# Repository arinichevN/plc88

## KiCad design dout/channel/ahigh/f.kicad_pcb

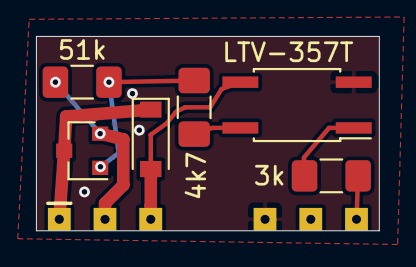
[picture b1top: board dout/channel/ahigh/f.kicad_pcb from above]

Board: 2 copper layers, 19.1 x 10.8 mm, 7 parts (0 on the bottom side), 8 nets.

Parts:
D1: 1N4148W; D_SOD-123
J1: dio_channel_i; dio_channel_im
Q1: BC807; SOT-23
R1: 51k; R_1206_3216Metric_Pad1.42x1.75mm_HandSolder
R2: 4k7; R_1206_3216Metric_Pad1.42x1.75mm_HandSolder
R3: 3k; R_1206_3216Metric_Pad1.42x1.75mm_HandSolder
U1: LTV-357T; SO-4_4.4x3.6mm_P2.54mm

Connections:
GND: J1.4, U1.2
IN: J1.6, R3.2
unnamed: Q1.1, R1.2, R2.1
unnamed: R2.2, U1.4
unnamed: R3.1, U1.1
OUT: D1.1, J1.1, Q1.3
VINM: D1.2, J1.3, U1.3
VINP: J1.2, Q1.2, R1.1

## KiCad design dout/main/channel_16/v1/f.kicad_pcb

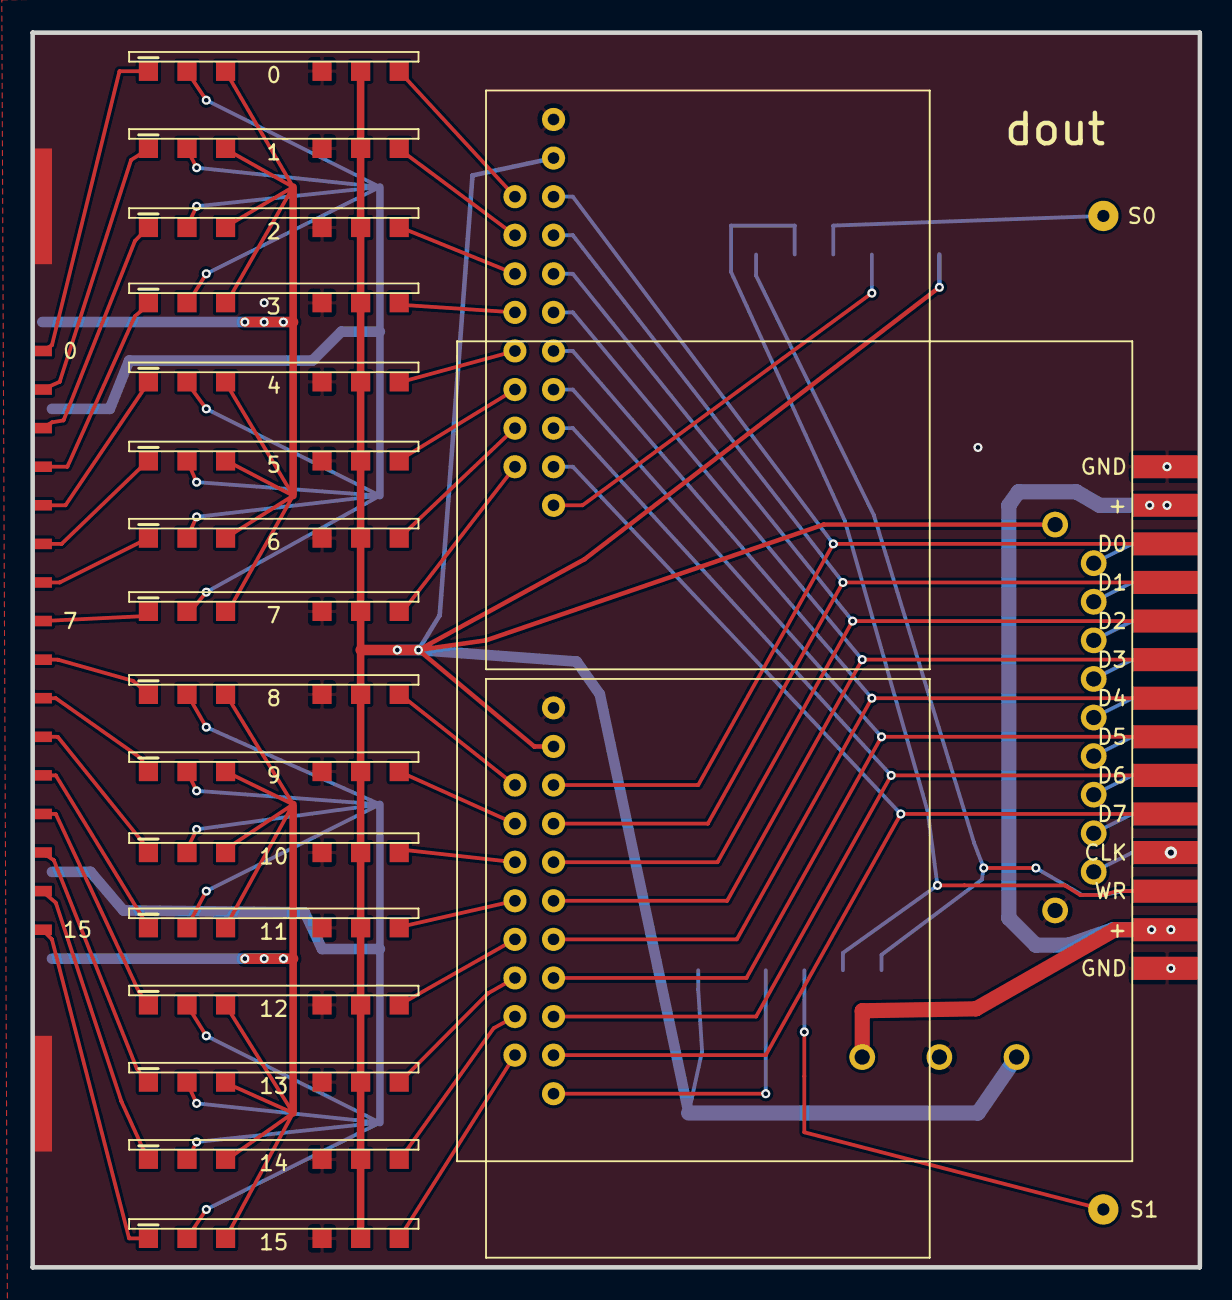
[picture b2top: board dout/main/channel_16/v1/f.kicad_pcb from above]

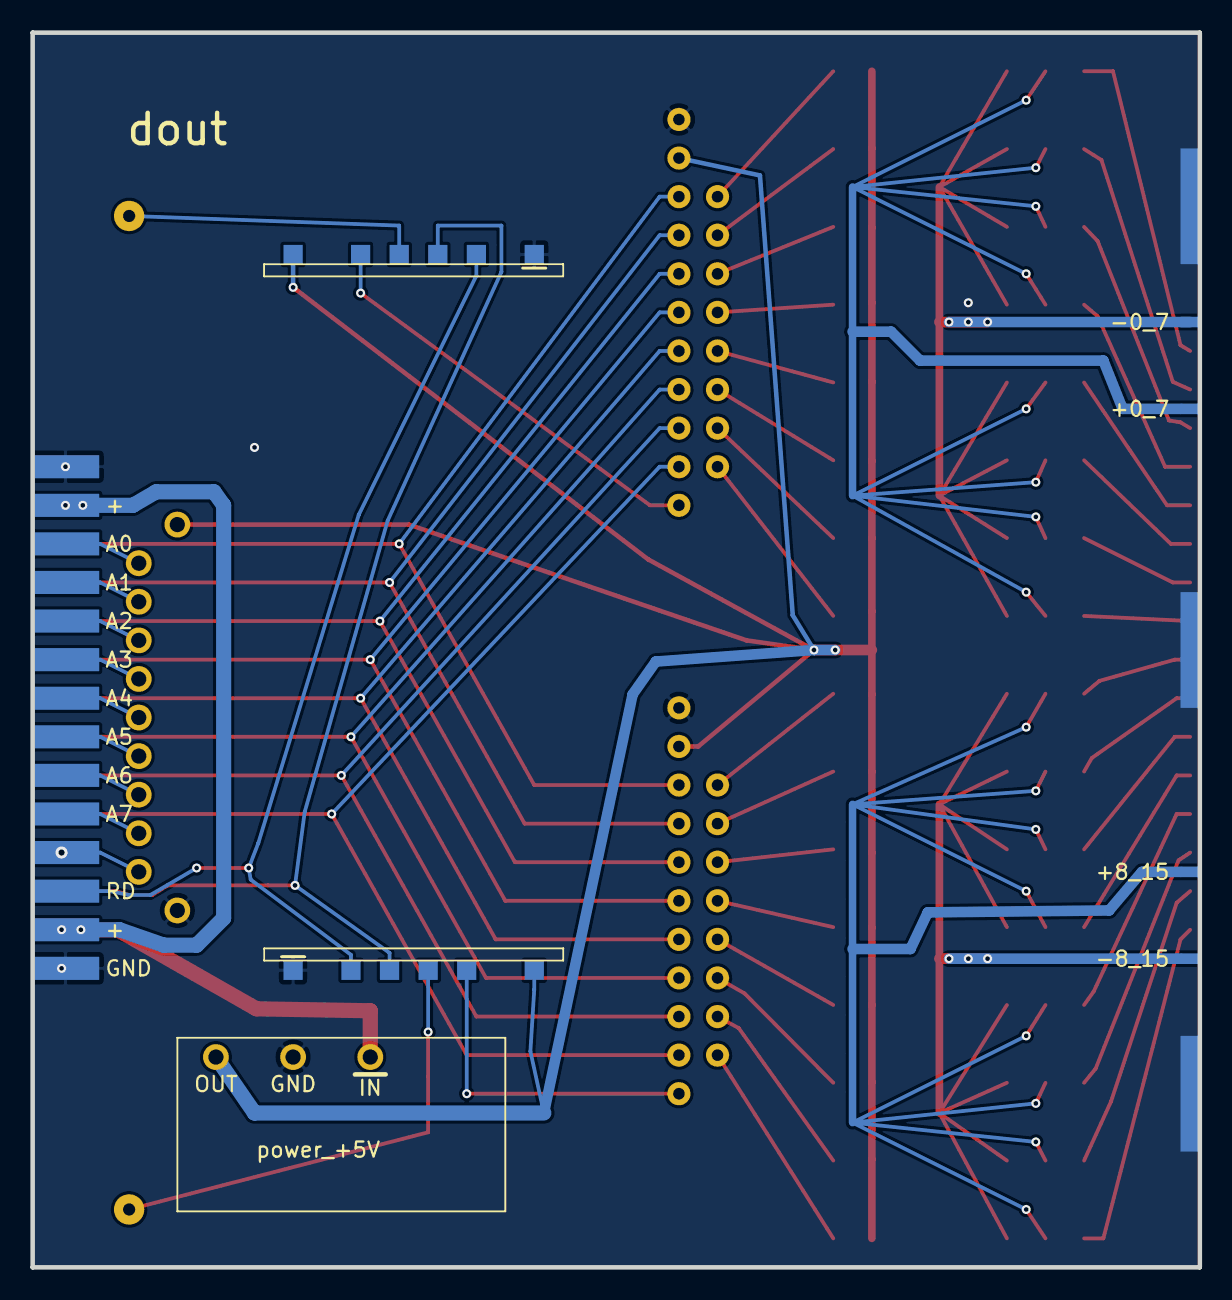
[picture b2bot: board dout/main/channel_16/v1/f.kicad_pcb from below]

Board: 2 copper layers, 76.8 x 81.3 mm, 26 parts (3 on the bottom side), 62 nets.

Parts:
J1: fm16_i; fm16_im
J2, J3, J4, J5, J6, J7, J8, J9, J10, J11, J12, J13, J14, J15, J16, J17: dio_channel_i
J18, J19: data_manager_i
J20, J21: wrs_i
J22: S0; SolderWirePad_1x01_Drill0.8mm
J23: S1; SolderWirePad_1x01_Drill0.8mm
J24: bus_i; bus_im
J25: selector4_i
J26: power_+5V; power_i

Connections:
+5V: J2.5, J3.5, J4.5, J5.5, J6.5, J7.5, J8.5, J9.5, J10.5, J11.5, J12.5, J13.5, J14.5, J15.5, J16.5, J17.5, J18.18, J19.18, J20.6, J21.6, J25.1, J26.2
A0: J24.5, J25.2
A1: J24.7, J25.3
A2: J24.9, J25.4
A3: J24.11, J25.5
A4: J24.13, J25.6
A5: J24.15, J25.7
A6: J24.17, J25.8
A7: J24.19, J25.9
CLK: J24.21, J24.22, J25.10
D0: J18.2, J19.2, J24.6
D1: J18.4, J19.4, J24.8
D2: J18.6, J19.6, J24.10
D3: J18.8, J19.8, J24.12
D4: J18.10, J19.10, J24.14
D5: J18.12, J19.12, J24.16
D6: J18.14, J19.14, J24.18
D7: J18.16, J19.16, J24.20
GND: J1.21, J1.22, J1.23, J1.24, J1.25, J2.4, J3.4, J4.4, J5.4, J6.4, J7.4, J8.4, J9.4, J10.4, J11.4, J12.4, J13.4, J14.4, J15.4, J16.4, J17.4, J18.17, J19.17, J20.1, J21.1, J24.1, J24.2, J24.27, J24.28, J25.11, J26.3
OPL0: J2.6, J18.1
OPL1: J3.6, J18.3
OPL2: J4.6, J18.5
OPL3: J5.6, J18.7
OPL4: J6.6, J18.9
OPL5: J7.6, J18.11
OPL6: J8.6, J18.13
OPL7: J9.6, J18.15
OPL8: J10.6, J19.1
OPL9: J11.6, J19.3
OPL10: J12.6, J19.5
OPL11: J13.6, J19.7
OPL12: J14.6, J19.9
OPL13: J15.6, J19.11
OPL14: J16.6, J19.13
OPL15: J17.6, J19.15
OUT0: J1.1, J2.1
OUT1: J1.2, J3.1
OUT2: J1.3, J4.1
OUT3: J1.4, J5.1
OUT4: J1.5, J6.1
OUT5: J1.6, J7.1
OUT6: J1.7, J8.1
OUT7: J1.8, J9.1
OUT8: J1.9, J10.1
OUT9: J1.10, J11.1
OUT10: J1.11, J12.1
OUT11: J1.12, J13.1
OUT12: J1.13, J14.1
OUT13: J1.14, J15.1
OUT14: J1.15, J16.1
OUT15: J1.16, J17.1
RD: J20.2, J21.2, J24.23
S0: J20.4, J22.1
S1: J21.4, J23.1
SW0: J18.19, J20.5
SW1: J19.19, J21.5
VM0_7: J1.17, J2.3, J3.3, J4.3, J5.3, J6.3, J7.3, J8.3, J9.3
VM8_15: J1.20, J10.3, J11.3, J12.3, J13.3, J14.3, J15.3, J16.3, J17.3
VP0_7: J1.18, J2.2, J3.2, J4.2, J5.2, J6.2, J7.2, J8.2, J9.2
VP8_15: J1.19, J10.2, J11.2, J12.2, J13.2, J14.2, J15.2, J16.2, J17.2
VPBUS: J24.3, J24.4, J24.25, J24.26, J26.1
WR: J20.3, J21.3, J24.24

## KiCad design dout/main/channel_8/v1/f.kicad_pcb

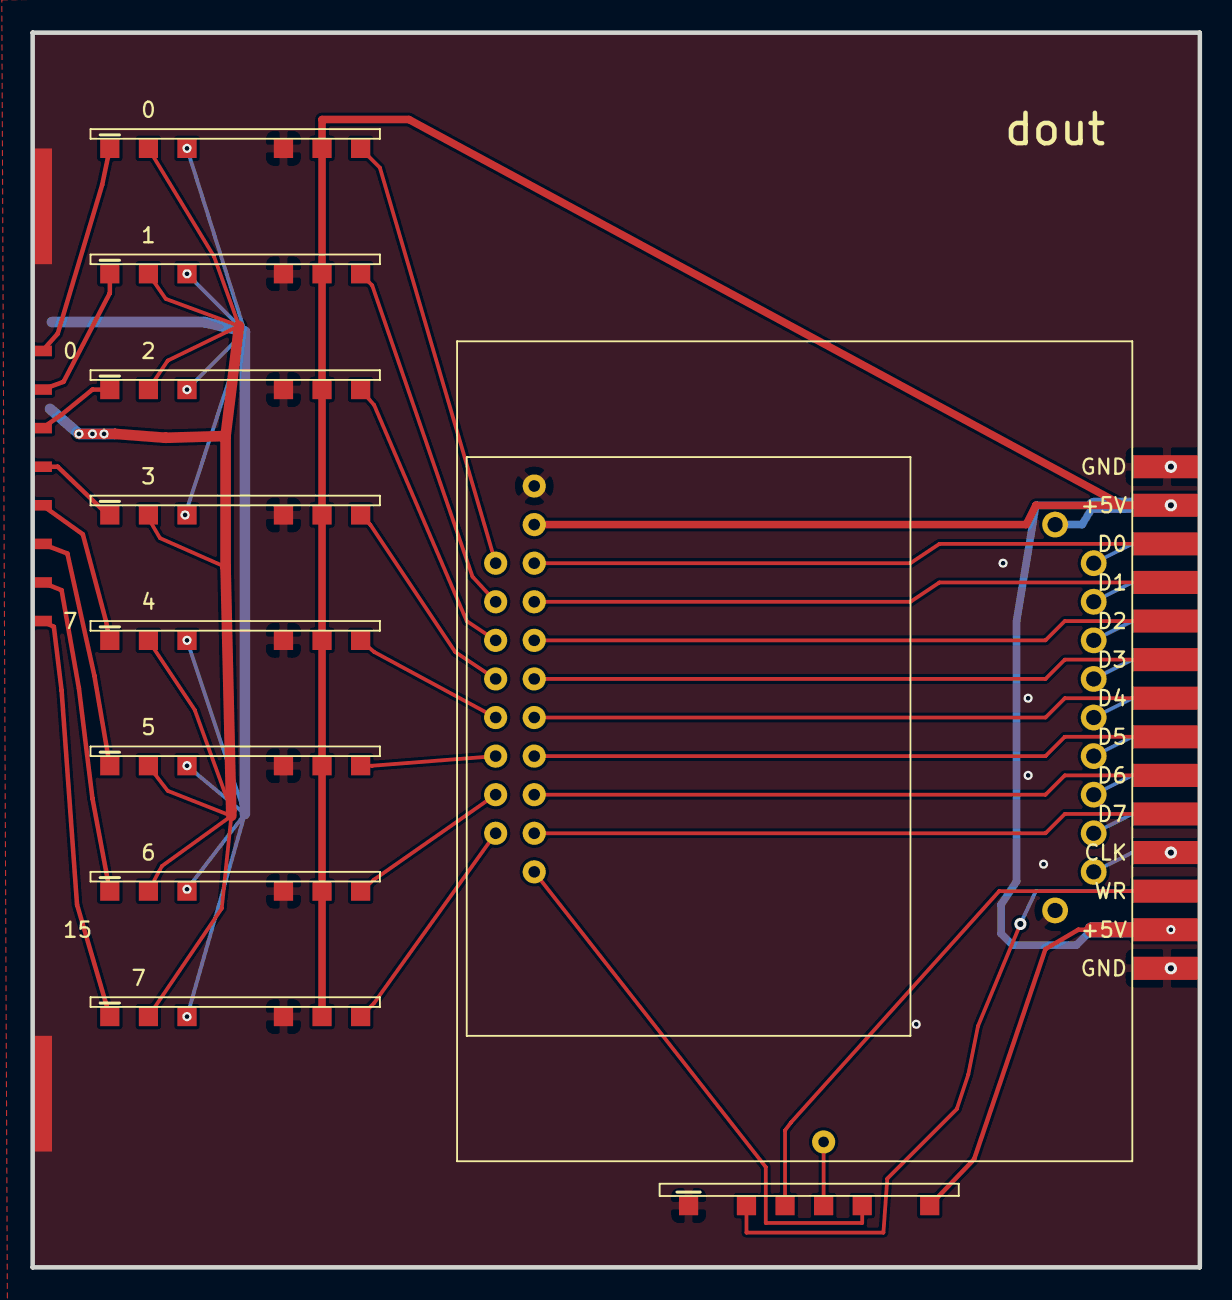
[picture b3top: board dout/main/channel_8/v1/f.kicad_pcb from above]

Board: 2 copper layers, 76.8 x 81.3 mm, 13 parts (0 on the bottom side), 41 nets.

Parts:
J1: fm16_i; fm16_im
J2, J3, J4, J5, J6, J7, J8, J9: dio_channel_i
J10: data_manager_i
J11: wrs_i
J12: selector4_i
J13: bus_i; bus_im

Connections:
+5V: J2.5, J3.5, J4.5, J5.5, J6.5, J7.5, J8.5, J9.5, J10.18, J11.6, J12.1, J13.3, J13.4, J13.25, J13.26
A0: J12.2, J13.5
A1: J12.3, J13.7
A2: J12.4, J13.9
A3: J12.5, J13.11
A4: J12.6, J13.13
A5: J12.7, J13.15
A6: J12.8, J13.17
A7: J12.9, J13.19
CLK: J12.10, J13.21, J13.22
D0: J10.2, J13.6
D1: J10.4, J13.8
D2: J10.6, J13.10
D3: J10.8, J13.12
D4: J10.10, J13.14
D5: J10.12, J13.16
D6: J10.14, J13.18
D7: J10.16, J13.20
GND: J1.21, J1.22, J1.23, J1.24, J1.25, J2.4, J3.4, J4.4, J5.4, J6.4, J7.4, J8.4, J9.4, J10.17, J11.1, J12.11, J13.1, J13.2, J13.27, J13.28
OPL0: J2.6, J10.1
OPL1: J3.6, J10.3
OPL2: J4.6, J10.5
OPL3: J5.6, J10.7
OPL4: J6.6, J10.9
OPL5: J7.6, J10.11
OPL6: J8.6, J10.13
OPL7: J9.6, J10.15
OUT0: J1.1, J2.1
OUT1: J1.2, J3.1
OUT2: J1.3, J4.1
OUT3: J1.4, J5.1
OUT4: J1.5, J6.1
OUT5: J1.6, J7.1
OUT6: J1.7, J8.1
OUT7: J1.8, J9.1
RD: J11.2, J13.23
S0: J11.4, J12.12
SW0: J10.19, J11.5
VM0_7: J1.17, J2.3, J3.3, J4.3, J5.3, J6.3, J7.3, J8.3, J9.3
VP0_7: J1.18, J2.2, J3.2, J4.2, J5.2, J6.2, J7.2, J8.2, J9.2
WR: J11.3, J13.24

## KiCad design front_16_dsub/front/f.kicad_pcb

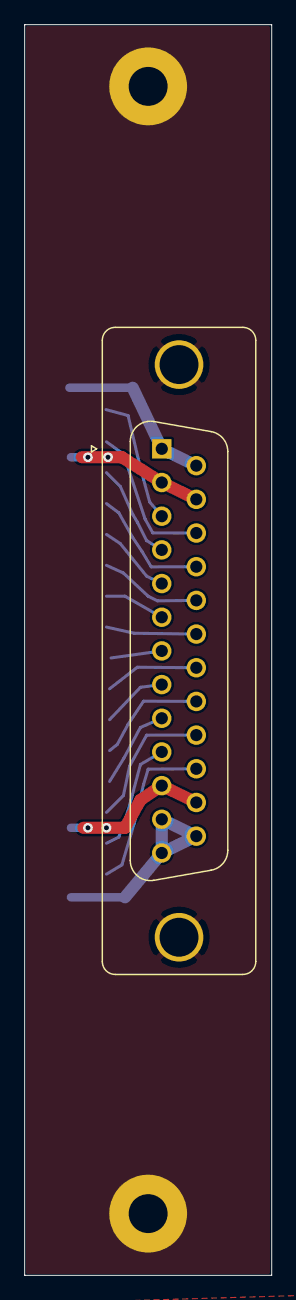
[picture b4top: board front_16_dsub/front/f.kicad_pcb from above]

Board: 2 copper layers, 20.3 x 102.9 mm, 4 parts (0 on the bottom side), 21 nets.

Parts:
H1, H2: MountingHole_Pad; MountingHole_3.2mm_M3_Pad
J1: fm16_i
J8: DB25_Female_MountingHoles; DSUB-25_Female_Vertical_P2.77x2.84mm_MountingHoles

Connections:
GND: H1.1, H2.1, J1.21, J1.22, J1.23, J1.24, J1.25, J8.0
GND0_7: J1.17, J8.1, J8.14
GND8_15: J1.20, J8.12, J8.13, J8.25
L0: J1.1, J8.3
L1: J1.2, J8.16
L2: J1.3, J8.4
L3: J1.4, J8.17
L4: J1.5, J8.5
L5: J1.6, J8.18
L6: J1.7, J8.6
L7: J1.8, J8.19
L8: J1.9, J8.7
L9: J1.10, J8.20
L10: J1.11, J8.8
L11: J1.12, J8.21
L12: J1.13, J8.9
L13: J1.14, J8.22
L14: J1.15, J8.10
L15: J1.16, J8.23
V0_7: J1.18, J8.2, J8.15
V8_15: J1.19, J8.11, J8.24

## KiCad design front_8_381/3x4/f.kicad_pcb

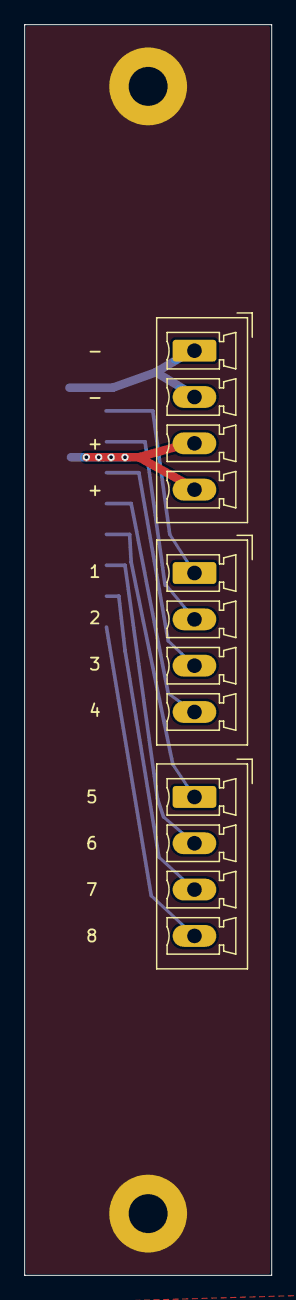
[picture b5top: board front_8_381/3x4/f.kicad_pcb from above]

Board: 2 copper layers, 20.3 x 102.9 mm, 6 parts (0 on the bottom side), 11 nets.

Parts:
H1, H2: MountingHole_Pad; MountingHole_3.2mm_M3_Pad
J1: fm16_i
J2, J3, J4: Conn_01x04; PhoenixContact_MCV_1,5_4-G-3.81_1x04_P3.81mm_Vertical

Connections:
GND: H1.1, H2.1, J1.21, J1.22, J1.23, J1.24, J1.25
L0: J1.1, J3.1
L1: J1.2, J3.2
L2: J1.3, J3.3
L3: J1.4, J3.4
L4: J1.5, J4.1
L5: J1.6, J4.2
L6: J1.7, J4.3
L7: J1.8, J4.4
VM0_7: J1.17, J2.1, J2.2
VP0_7: J1.18, J2.3, J2.4

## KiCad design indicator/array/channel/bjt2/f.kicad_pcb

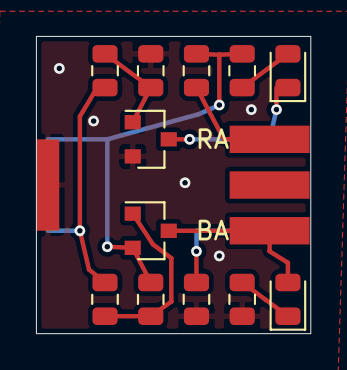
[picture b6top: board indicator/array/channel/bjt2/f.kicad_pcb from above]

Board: 2 copper layers, 15.2 x 16.5 mm, 14 parts (0 on the bottom side), 11 nets.

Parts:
D1, D2: LED; LED_0805_2012Metric
J1: indicator_channel_in_i; indicator_channel_in_im
J2: indicator_channel_out_i
Q1: BC817; SOT-23
Q2: BC807; SOT-23
R1, R8: 100k; R_0805_2012Metric
R2, R5: 51k; R_0805_2012Metric
R3, R7: 2k; R_0805_2012Metric
R4, R6: 10k; R_0805_2012Metric

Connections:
BLUE_A: D2.2, J2.3, Q2.3
BLUE_K: J2.4, R7.1
GND: J1.3, Q1.2, R1.1, R6.2, R7.2
IN: J1.2, R2.1, R5.2
unnamed: D1.2, R4.2
unnamed: D2.1, R6.1
unnamed: Q1.1, R1.2, R2.2
unnamed: Q2.1, R5.1, R8.1
RED_A: J2.1, R3.2
RED_K: D1.1, J2.2, Q1.3
VIN: J1.1, Q2.2, R3.1, R4.1, R8.2
